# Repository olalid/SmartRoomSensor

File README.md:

# SmartRoomSensor
Smarter replacement for the RG20 room sensor that is an optional extra for some older NIBE heat pumps.

The NIBE RG20 room sensor is a very simple thermostat like device that is connected to a NIBE heatpump and lets you control the temperature in your home more preciesely. A little simplified the original consists of a potentiometer and an NTC resistor.

This replacement version has MQTT support and lets you control the setpoint and read back the current temperature from your home automation system. It also shows the status (heating or idle) of the heatpump.
It connects to the same interface in the heatpump as the RG20 does plus that it steals some power from the heatpump internal PSU (which is around 20-24V).

The hardware is based on on an ESP8266 module, the ESP-12F, combining it with a digital potentiometer for the setpoint control and an NTC resistor for temperature reading. The heatpump power supply has reduced voltage when the heatpump is active, so measuring that voltage makes it possible to detect if the heatpumpt is active or not.

Ths software is based on Arduino and support libraries WiFiManager and PubSubClinet.
A minor modification to PubSubClient is needed, so the modified file is also included.

PS. This is currently work in progress. The uploaded version of schematics and PCB has not been built as a complete prototype, but rather as a patched version of an older PCB revision. I.e. it is not 100% guranteed that it works, even if the risk that it does not should be small.

# Prerequisites
To use this unit, you need to have:

A NIBE heatpump that is compatible with the RG20 room sensor (Doh!)

An MQTT server (like mosquitto) running on a server somewhere.

Some kind of home automation software to display a user interface and possibly atuomate the control of the unit (like Home Assistant).

# Programming
To program the unit, you will need an FTDI USB cable with part number TTL-232R-3V3 (Farnell 1329311). Connect this to the 6-pin header (JP1) and use Arduino (or equivalent) to download the software.

# How to connect to the heatpump
The sensor has a screw terminal that is used to connect wires coming from the heatpump.
The marking on the PCB is the same as the original RG20, plus the additional terminal for the power.
See the installation manual for the original sensor for connection to the heat pump.
http://www.nibe.se/nibedocuments/10013/011022-6.pdf

One thing is different, the power connection is marked with "+" next to its screw terminal on the PCB, but in the heat pump there is no easy accessible terminal for this. So, instead we connect to one of the solder pins on an IDC header that carries the voltage we want to access. A probe clip, such as Farnell part number 523525 makes this easier.

# How to configure the unit
When intially powered up the unit will start in access point mode, creating a WiFi network called "SmartRoomSensor".
Connect to this network using a computer or a smartphone.

Normally a web browser with the configuration interface should open automatically and you can enter the configuration details needed.

You will need to enter the name of your Wifi network, the password, the MQTT server IP or name, MQTT server username/password (if any) and the topics for MQTT.

There are 4 MQTT topics:

tset: the topic the unit will subscribe to get updates on target temperature.

tget: the topic where the unit will publish the configured target temperature.

cget: the topic where the unit will publish the current measured temperature.

mode: the topic where the unit will publish the current heatpump mode (heat or idle).

# Gotchas
The unit wakes up once a minute to set and read temperatures.
Which means that there may be a delay of up to one minute when you set the temperature until it is updated on the heatpumps display.
It may seem unecessary to use sleep mode in this application, but without doing this, the unit would get far to hot and the temperature readings would be useless.

# Known problems
The unit does heat up a bit, compared to the surrounding room temperature, which results in a temperature reading that is 1-2 degrees more than the actual temperature. So the target temperature needs to be increased accordingly. I.e. if you want to have 21 degrees in the room, set 22 or 23 degrees.
This could possibly be compensated by increasing the value of R2 slightly, but this has not (yet) been tested.

# Enclosure
The unit fits in a Supertronic PP42 enclosure. This is also sold as Qubino ZMNHGA1.
See https://www.m.nu/tillbehor/plastbox-vit-med-lufthal-for-vaggmontering

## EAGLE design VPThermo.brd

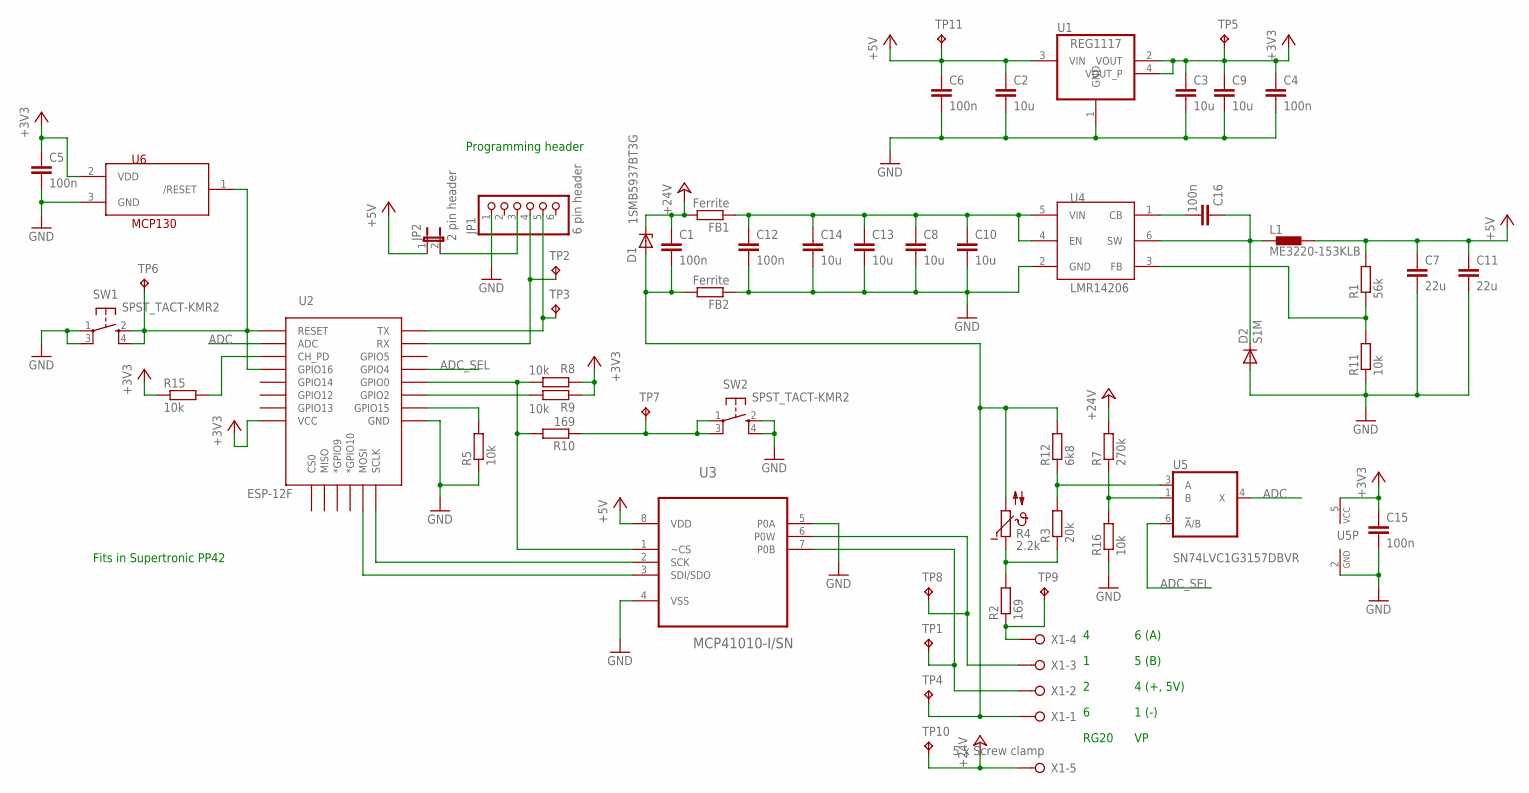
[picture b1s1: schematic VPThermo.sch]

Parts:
C1, C4, C5, C6, C12, C15, C16: 100n; C0603
C2, C3, C8, C9, C10, C13, C14: 10u; C0805
C7, C11: 22u; C0805
D1: 1SMB5937BT3G; SMB
D2: S1M; SMA
FB1, FB2: Ferrite; R0603
JP1: 6 pin header; 1X06
JP2: 2 pin header; JP1
L1: ME3220-153KLB; SDR0302
R1: 56k; R0603
R2, R10: 169; R0603
R3: 20k; R0603
R4: 2.2k; P640
R5, R8, R9, R11, R15, R16: 10k; R0603
R7: 270k; R0603
R12: 6k8; R0603
SW1, SW2: SPST_TACT-KMR2; KMR2
TP1, TP2, TP3, TP4, TP5, TP6, TP7, TP8, TP9, TP10, TP11: TPB1,27; B1,27
U1: REG1117; SOT223
U2: ESP-12F; ESP12E-SMD
U3: MCP41010-I/SN; SOIC127P600X175-8N; MPN MCP41010-I/SN
U4: LMR14206; SOT-23-6
U5: SN74LVC1G3157DBVR; DBV_R-PDSO-G6
U6: MCP130; SOT23
X1: 5 x Screw clamp; W237-5P

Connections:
+3V3: C3.1, C4.1, C5.1, C9.1, C15.1, R8.1, R9.1, R15.1, TP5.TP, U1.2 (VOUT), U1.4 (VOUT_P), U2.VCC, U5.5 (VCC), U6.2 (VDD)
+5V: C2.1, C6.1, C7.1, C11.1, JP2.1, L1.2, R1.2, TP11.TP, U1.3 (VIN), U3.8 (VDD)
+24V: C1.1, D1.C, FB1.2, R7.2, TP10.TP, X1.5
ADC: U2.ADC, U5.4 (X)
ADC_SEL: U2.GPIO4, U5.6 (!A!/B)
GND: C2.2, C3.2, C4.2, C5.2, C6.2, C7.2, C8.2, C9.2, C10.2, C11.2, C12.2, C13.2, C14.2, C15.2, D2.A, FB2.1, JP1.1, R5.1, R11.1, R16.1, SW1.1, SW1.3 (P1), SW2.2 (S), SW2.4 (S1), U1.1 (GND), U2.GND, U3.4 (VSS), U3.5 (P0A), U4.2 (GND), U5.2 (GND), U6.3 (GND)
unnamed: R10.1, SW2.1, SW2.3 (P1), TP7.TP
unnamed: U2.MOSI, U3.3 (SDI/SDO)
unnamed: C16.2, U4.1 (CB)
unnamed: JP1.3, JP2.2
unnamed: U2.SCLK, U3.2 (SCK)
unnamed: JP1.4, TP2.TP, U2.RXD0 (RX)
unnamed: JP1.5, TP3.TP, U2.TXD0 (TX)
unnamed: R3.2, R12.1, U5.3 (A)
unnamed: TP8.TP, U3.6 (P0W), X1.3
unnamed: R2.2, R3.1, R4.1
unnamed: R2.1, TP9.TP, X1.4
unnamed: R5.2, U2.GPIO15
unnamed: C8.1, C10.1, C12.1, C13.1, C14.1, FB1.1, U4.4 (EN), U4.5 (VIN)
unnamed: TP1.TP, U3.7 (P0B), X1.2
unnamed: R8.2, R10.2, U2.GPIO0, U3.1 (~CS)
unnamed: R9.2, U2.GPIO2
unnamed: C1.2, D1.A, FB2.2, R4.2, R12.2, TP4.TP, X1.1
unnamed: R1.1, R11.2, U4.3 (FB)
unnamed: R15.2, U2.CH_PD
unnamed: R7.1, R16.2, U5.1 (B)
unnamed: SW1.2 (S), SW1.4 (S1), TP6.TP, U2.GPIO16, U2.RESET, U6.1 (/RESET)
unnamed: C16.1, D2.C, L1.1, U4.6 (SW)

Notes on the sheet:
RG20
1 (-)
4 (+, 5V)
5 (B)
6 (A)
Fits in Supertronic PP42
Programming header

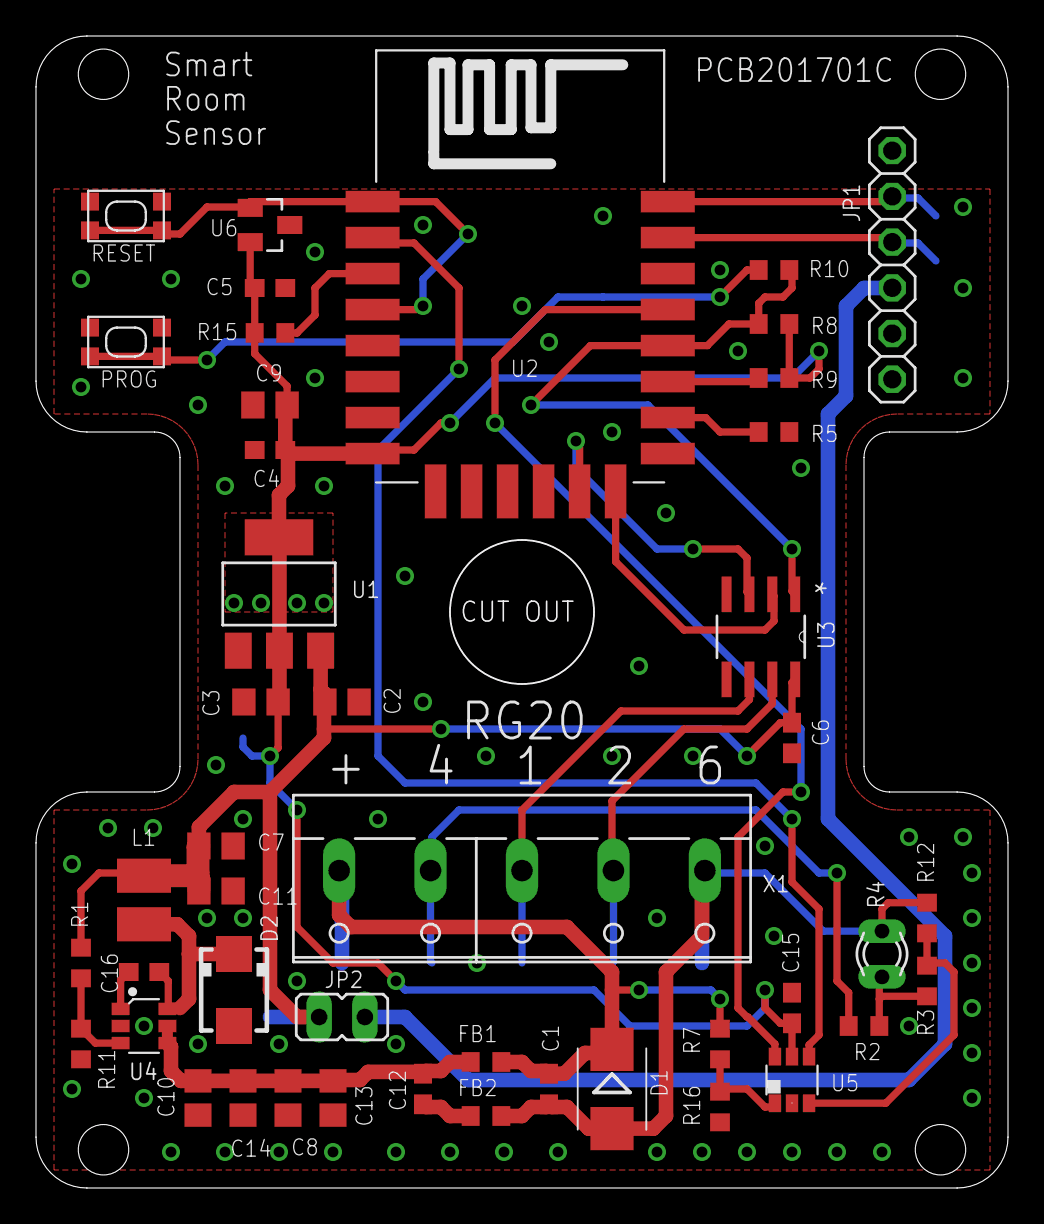
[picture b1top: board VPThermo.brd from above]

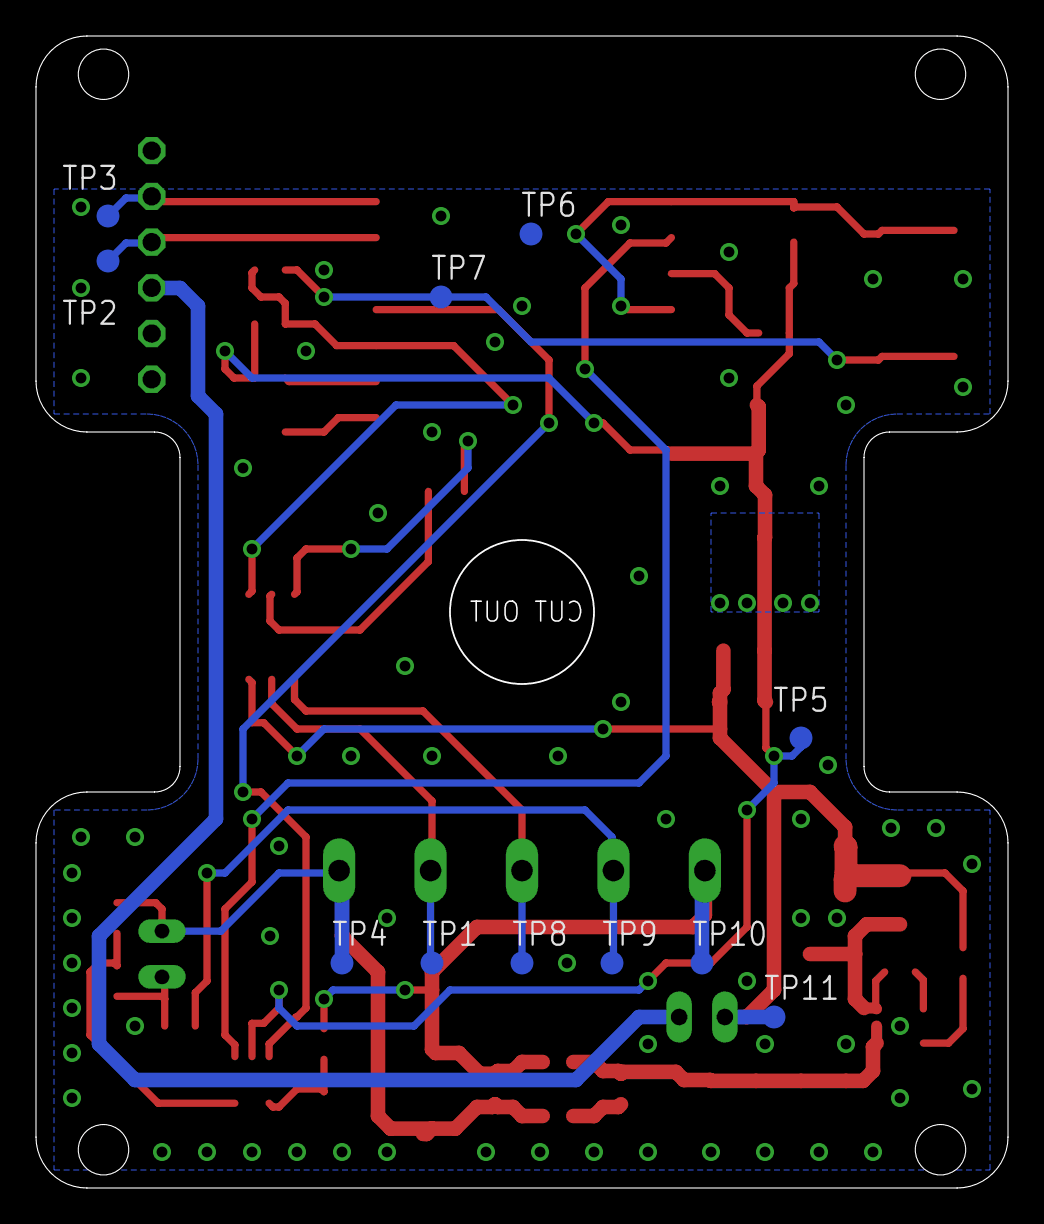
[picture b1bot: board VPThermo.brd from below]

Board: 2 copper layers, 53.9 x 63.9 mm, 56 parts (11 on the bottom side), 28 nets.

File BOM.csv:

Qty;Parts;Value;Description;Farnell order code;m.nu order code
7;C1, C4, C5, C6, C12, C15, C16;100n;CAPACITOR, European symbol;1759122;
6;R5, R8, R9, R11, R15, R16;10k;RESISTOR, European symbol;2447230;
7;C2, C3, C8, C9, C10, C13, C14;10u;CAPACITOR, European symbol;2611943;
2;R2, R10;169R;RESISTOR, European symbol;2303081;
1;D1;1SMB5937BT3G;Z-Diode;1431179;
1;JP2;2 pin header;JUMPER;1593411;
1;R4;2.2k;PHILIPS NTC;1187025;
1;R3;20k;RESISTOR, European symbol;2447293;
2;C7, C11;22u;CAPACITOR, European symbol;2309030;
1;R7;270k;RESISTOR, European symbol;2447313;
1;X1;5 x Screw clamp;WAGO SREW CLAMP;1717004;
1;R1;56k;RESISTOR, European symbol;2303215;
1;JP1;6 pin header;PIN HEADER;1593415;
1;R12;6k8;RESISTOR, European symbol;2447427;
1;U2;ESP-12F;ESP12F Module;;ESP12F
2;FB1, FB2;Ferrite;RESISTOR, European symbol;1635706;
1;U4;LMR14206;LMR14206 SIMPLE SWITCHER® 42Vin, 0.6A Step-Down Voltage Regulator in SOT-23;2064681;
1;U6;MCP130T-315I/TT;Reset circuit;9758470;
1;U3;MCP41010-I/SN;Digital POT;9758607;
1;L1;ME3220-153KLB;Inductor;2287926;
1;U1;REG1117;800mA and 1A Low Dropout (LDO) Positive Regulator;1825376;
1;D2;S1A;Schottky diode;1559148;
1;U5;SN74LVC1G3157DBVR;Single-Pole, Double-Throw Analog Switch;1470910;
2;SW1, SW2;SPST_TACT-KMR2;SMT 6mm switch, EVQQ2 series;1437636;

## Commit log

2018-02-03 Updated to support idle detection
2018-02-08 Revision C
2018-02-08 Image of rev C PCB
2018-02-08 Cleaned up a bit.
2018-02-08 Patched version of PubSubClient source code
2018-02-08 Example configuration for Home Assistant
2018-02-08 Home Assistant example UI
2018-02-08 Bill of Materials
